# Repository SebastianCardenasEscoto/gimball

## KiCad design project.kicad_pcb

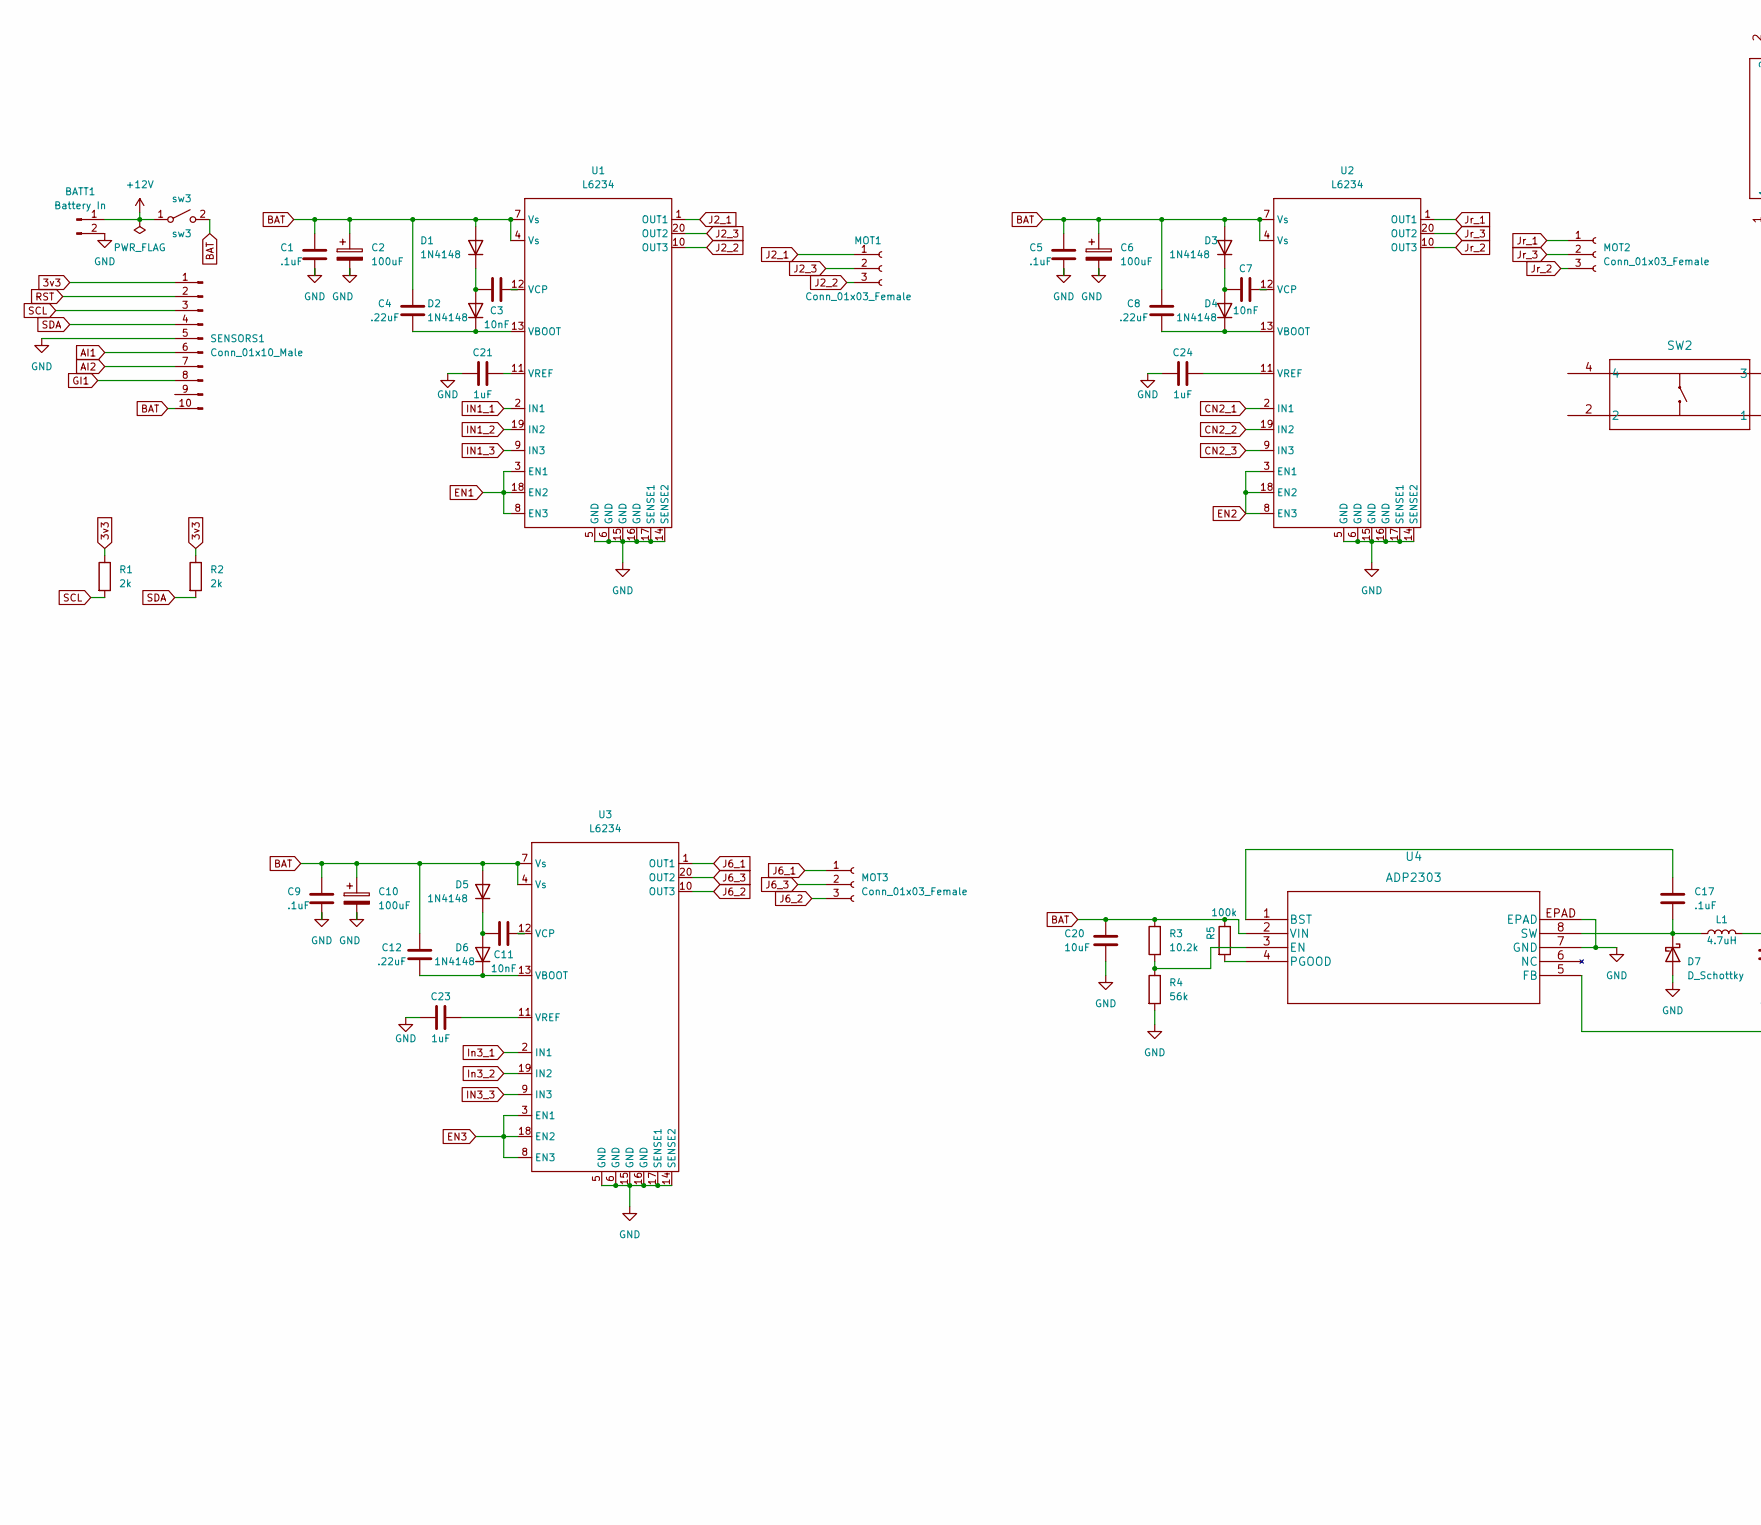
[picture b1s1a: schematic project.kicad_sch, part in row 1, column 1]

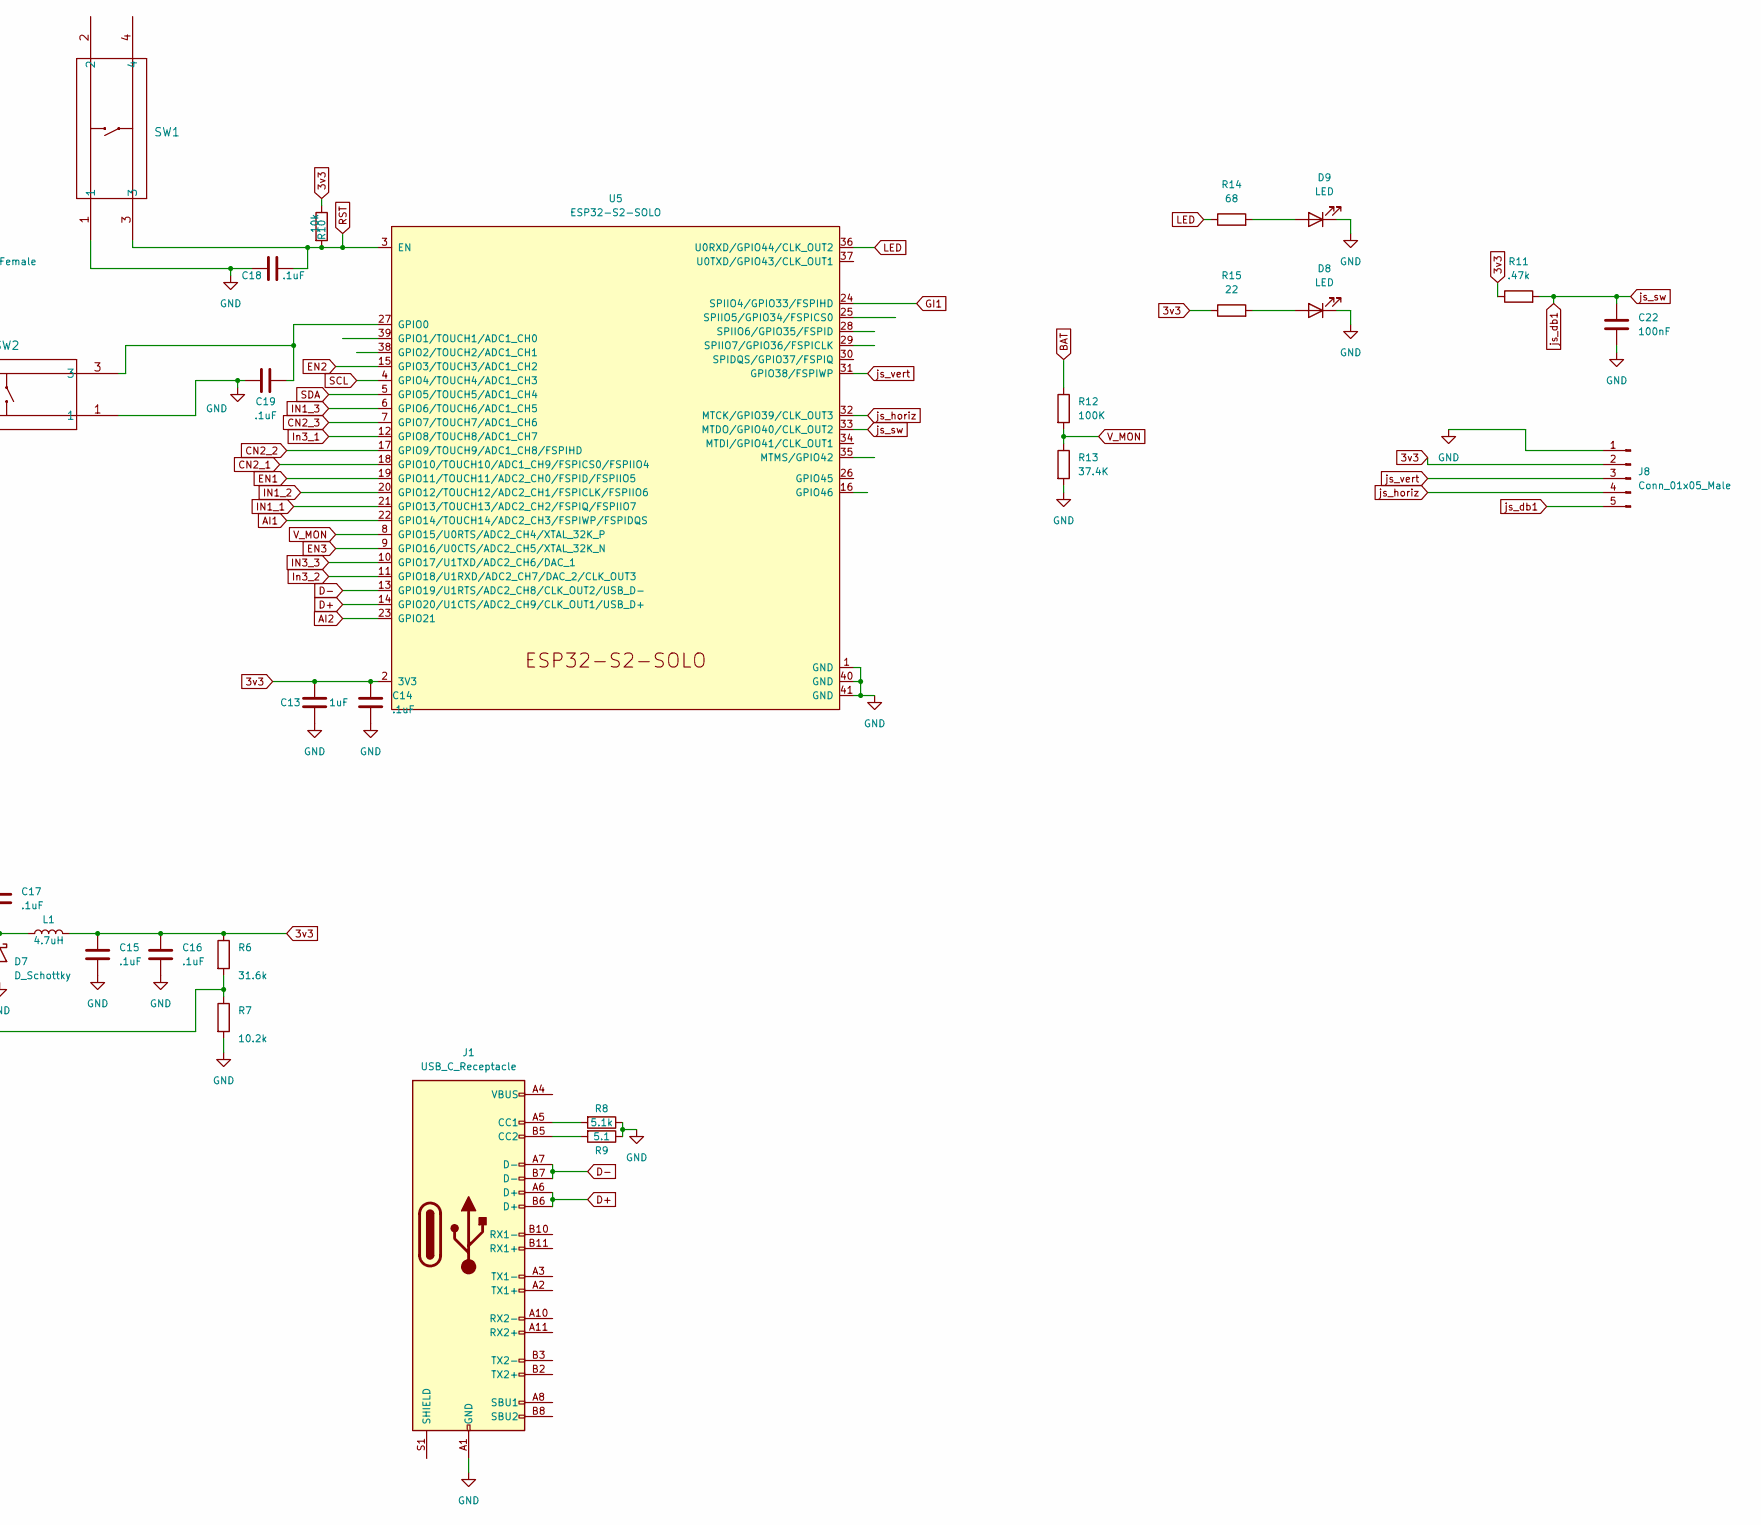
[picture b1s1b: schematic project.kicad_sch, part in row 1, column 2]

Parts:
BATT1: Battery In; kill_switch
C1, C5, C9, C14, C15, C16, C17, C18, C19: .1uF; C_0603_1608Metric
C2, C6, C10: 100uF; 35TZV100M6.3X8
C3, C7, C11: 10nF; C_0603_1608Metric
C4, C8, C12: .22uF; C_0603_1608Metric
C13, C21, C23, C24: 1uF; C_0603_1608Metric
C20: 10uF; C_0603_1608Metric
C22: 100nF; C_0603_1608Metric
D1, D2, D3, D4, D5, D6: 1N4148; D_SOD-123
D7: D_Schottky; D_0603_1608Metric_Pad1.05x0.95mm_HandSolder
D8, D9: LED; LED_0603_1608Metric_Pad1.05x0.95mm_HandSolder
J1: USB_C_Receptacle; USB4105-GF-A
J8: Conn_01x05_Male; JST_XH_B5B-XH-A_1x05_P2.50mm_Vertical
L1: 4.7uH; L_0603_1608Metric_Pad1.05x0.95mm_HandSolder
MOT1, MOT2, MOT3: Conn_01x03_Female
R1, R2: 2k; R_0603_1608Metric_Pad0.98x0.95mm_HandSolder
R3, R7: 10.2k; R_0603_1608Metric_Pad0.98x0.95mm_HandSolder
R4: 56k; R_0603_1608Metric_Pad0.98x0.95mm_HandSolder
R5: 100k; R_0603_1608Metric_Pad0.98x0.95mm_HandSolder
R6: 31.6k; R_0603_1608Metric_Pad0.98x0.95mm_HandSolder
R8: 5.1k; R_0603_1608Metric_Pad0.98x0.95mm_HandSolder
R9: 5.1; R_0603_1608Metric_Pad0.98x0.95mm_HandSolder
R10: 10k; R_0603_1608Metric_Pad0.98x0.95mm_HandSolder
R11: .47k; R_0603_1608Metric_Pad0.98x0.95mm_HandSolder
R12: 100K; R_0603_1608Metric_Pad0.98x0.95mm_HandSolder
R13: 37.4K; R_0603_1608Metric_Pad0.98x0.95mm_HandSolder
R14: 68; R_0603_1608Metric_Pad0.98x0.95mm_HandSolder
R15: 22; R_0603_1608Metric_Pad0.98x0.95mm_HandSolder
SENSORS1: Conn_01x10_Male
SW1, SW2: PTS647SM38SMTR2LFS
U1, U2, U3: L6234; DIP-20_W7.62mm_Socket
U4: ADP2303; ADP2303ARDZ-3.3-R7
U5: ESP32-S2-SOLO
sw3: sw3; kill_switch

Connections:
3v3: C13.1, C14.1, C15.1, C16.1, J8.2, L1.2, R1.1, R2.1, R6.1, R10.1, R11.1, R15.1, SENSORS1.1, U5.2 (3V3)
+12V: BATT1.1, sw3.1 (A)
AI1: SENSORS1.6, U5.22 (GPIO14/TOUCH14/ADC2_CH3/FSPIWP/FSPIDQS)
AI2: SENSORS1.7, U5.23 (GPIO21)
BAT: C1.1, C2.1, C4.2, C5.1, C6.1, C8.2, C9.1, C10.1, C12.2, C20.1, D1.2 (A), D3.2 (A), D5.2 (A), R3.1, R5.1, R12.1, SENSORS1.10, U1.4 (Vs), U1.7 (Vs), U2.4 (Vs), U2.7 (Vs), U3.4 (Vs), U3.7 (Vs), U4.2 (VIN), sw3.2 (B)
CN2_1: U2.2 (IN1), U5.18 (GPIO10/TOUCH10/ADC1_CH9/FSPICS0/FSPIIO4)
CN2_2: U2.19 (IN2), U5.17 (GPIO9/TOUCH9/ADC1_CH8/FSPIHD)
CN2_3: U2.9 (IN3), U5.7 (GPIO7/TOUCH7/ADC1_CH6)
D+: J1.A6 (D+), J1.B6 (D+), U5.14 (GPIO20/U1CTS/ADC2_CH9/CLK_OUT1/USB_D+)
D-: J1.A7 (D-), J1.B7 (D-), U5.13 (GPIO19/U1RTS/ADC2_CH8/CLK_OUT2/USB_D-)
EN1: U1.3 (EN1), U1.8 (EN3), U1.18 (EN2), U5.19 (GPIO11/TOUCH11/ADC2_CH0/FSPID/FSPIIO5)
EN2: U2.3 (EN1), U2.8 (EN3), U2.18 (EN2), U5.15 (GPIO3/TOUCH3/ADC1_CH2)
EN3: U3.3 (EN1), U3.8 (EN3), U3.18 (EN2), U5.9 (GPIO16/U0CTS/ADC2_CH5/XTAL_32K_N)
GI1: SENSORS1.8, U5.24 (SPIIO4/GPIO33/FSPIHD)
GND: BATT1.2, C1.2, C2.2, C5.2, C6.2, C9.2, C10.2, C13.2, C14.2, C15.2, C16.2, C18.1, C19.1, C20.2, C21.1, C22.2, C23.1, C24.1, D7.2 (A), D8.1 (K), D9.1 (K), J1.A1 (GND), J1.A12 (GND), J1.B1 (GND), J1.B12 (GND), J8.1, R4.2, R7.2, R8.1, R9.1, R13.2, SENSORS1.5, SW1.1, SW2.1, U1.5 (GND), U1.6 (GND), U1.14 (SENSE2), U1.15 (GND), U1.16 (GND), U1.17 (SENSE1), U2.5 (GND), U2.6 (GND), U2.14 (SENSE2), U2.15 (GND), U2.16 (GND), U2.17 (SENSE1), U3.5 (GND), U3.6 (GND), U3.14 (SENSE2), U3.15 (GND), U3.16 (GND), U3.17 (SENSE1), U4.7 (GND), U4.EPAD, U5.1 (GND), U5.40 (GND), U5.41 (GND)
IN1_1: U1.2 (IN1), U5.21 (GPIO13/TOUCH13/ADC2_CH2/FSPIQ/FSPIIO7)
IN1_2: U1.19 (IN2), U5.20 (GPIO12/TOUCH12/ADC2_CH1/FSPICLK/FSPIIO6)
IN1_3: U1.9 (IN3), U5.6 (GPIO6/TOUCH6/ADC1_CH5)
IN3_3: U3.9 (IN3), U5.10 (GPIO17/U1TXD/ADC2_CH6/DAC_1)
In3_1: U3.2 (IN1), U5.12 (GPIO8/TOUCH8/ADC1_CH7)
In3_2: U3.19 (IN2), U5.11 (GPIO18/U1RXD/ADC2_CH7/DAC_2/CLK_OUT3)
J2_1: MOT1.1, U1.1 (OUT1)
J2_2: MOT1.3, U1.10 (OUT3)
J2_3: MOT1.2, U1.20 (OUT2)
J6_1: MOT3.1, U3.1 (OUT1)
J6_2: MOT3.3, U3.10 (OUT3)
J6_3: MOT3.2, U3.20 (OUT2)
Jr_1: MOT2.1, U2.1 (OUT1)
Jr_2: MOT2.3, U2.10 (OUT3)
Jr_3: MOT2.2, U2.20 (OUT2)
LED: R14.1, U5.36 (U0RXD/GPIO44/CLK_OUT2)
unnamed: C3.1, D1.1 (K), D2.2 (A)
unnamed: C3.2, U1.12 (VCP)
unnamed: C4.1, D2.1 (K), U1.13 (VBOOT)
unnamed: C7.1, D3.1 (K), D4.2 (A)
unnamed: C7.2, U2.12 (VCP)
unnamed: C8.1, D4.1 (K), U2.13 (VBOOT)
unnamed: C11.1, D5.1 (K), D6.2 (A)
unnamed: C11.2, U3.12 (VCP)
unnamed: C12.1, D6.1 (K), U3.13 (VBOOT)
unnamed: C17.1, U4.1 (BST)
unnamed: C17.2, D7.1 (K), L1.1, U4.8 (SW)
unnamed: C19.2, SW2.3, U5.27 (GPIO0)
unnamed: C21.2, U1.11 (VREF)
unnamed: C23.2, U3.11 (VREF)
unnamed: C24.2, U2.11 (VREF)
unnamed: D8.2 (A), R15.2
unnamed: D9.2 (A), R14.2
unnamed: J1.A5 (CC1), R8.2
unnamed: J1.B5 (CC2), R9.2
unnamed: R3.2, R4.1, U4.3 (EN)
unnamed: R5.2, U4.4 (PGOOD)
unnamed: R6.2, R7.1, U4.5 (FB)
RST: C18.2, R10.2, SENSORS1.2, SW1.3, U5.3 (EN)
SCL: R1.2, SENSORS1.3, U5.4 (GPIO4/TOUCH4/ADC1_CH3)
SDA: R2.2, SENSORS1.4, U5.5 (GPIO5/TOUCH5/ADC1_CH4)
V_MON: R12.2, R13.1, U5.8 (GPIO15/U0RTS/ADC2_CH4/XTAL_32K_P)
js_db1: C22.1, J8.5, R11.2, U5.33 (MTDO/GPIO40/CLK_OUT2)
js_horiz: J8.4, U5.32 (MTCK/GPIO39/CLK_OUT3)
js_vert: J8.3, U5.31 (GPIO38/FSPIWP)

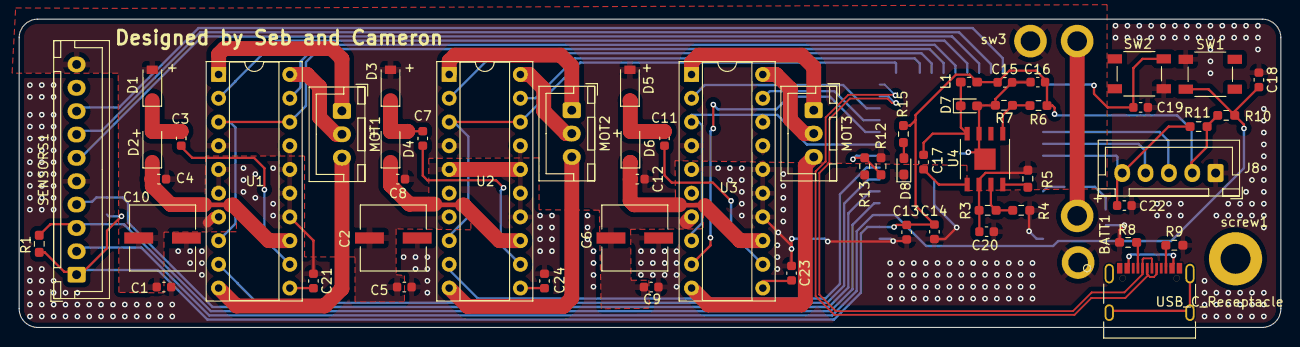
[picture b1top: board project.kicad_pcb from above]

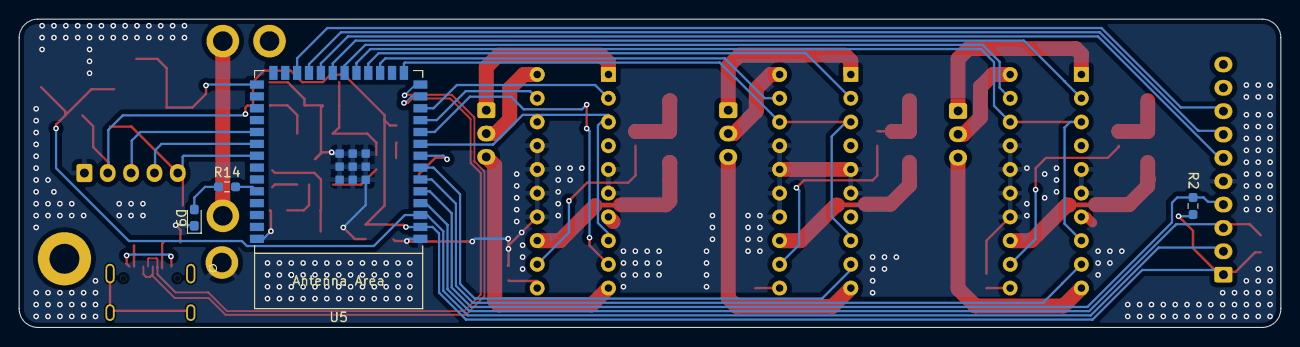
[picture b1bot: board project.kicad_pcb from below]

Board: 2 copper layers, 135.1 x 33.0 mm, 64 parts (4 on the bottom side), 60 nets.

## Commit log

2023-09-10 project

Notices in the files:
parts and their libraries:
Copyright 2021 Accelerated Designs. All rights reserved.
